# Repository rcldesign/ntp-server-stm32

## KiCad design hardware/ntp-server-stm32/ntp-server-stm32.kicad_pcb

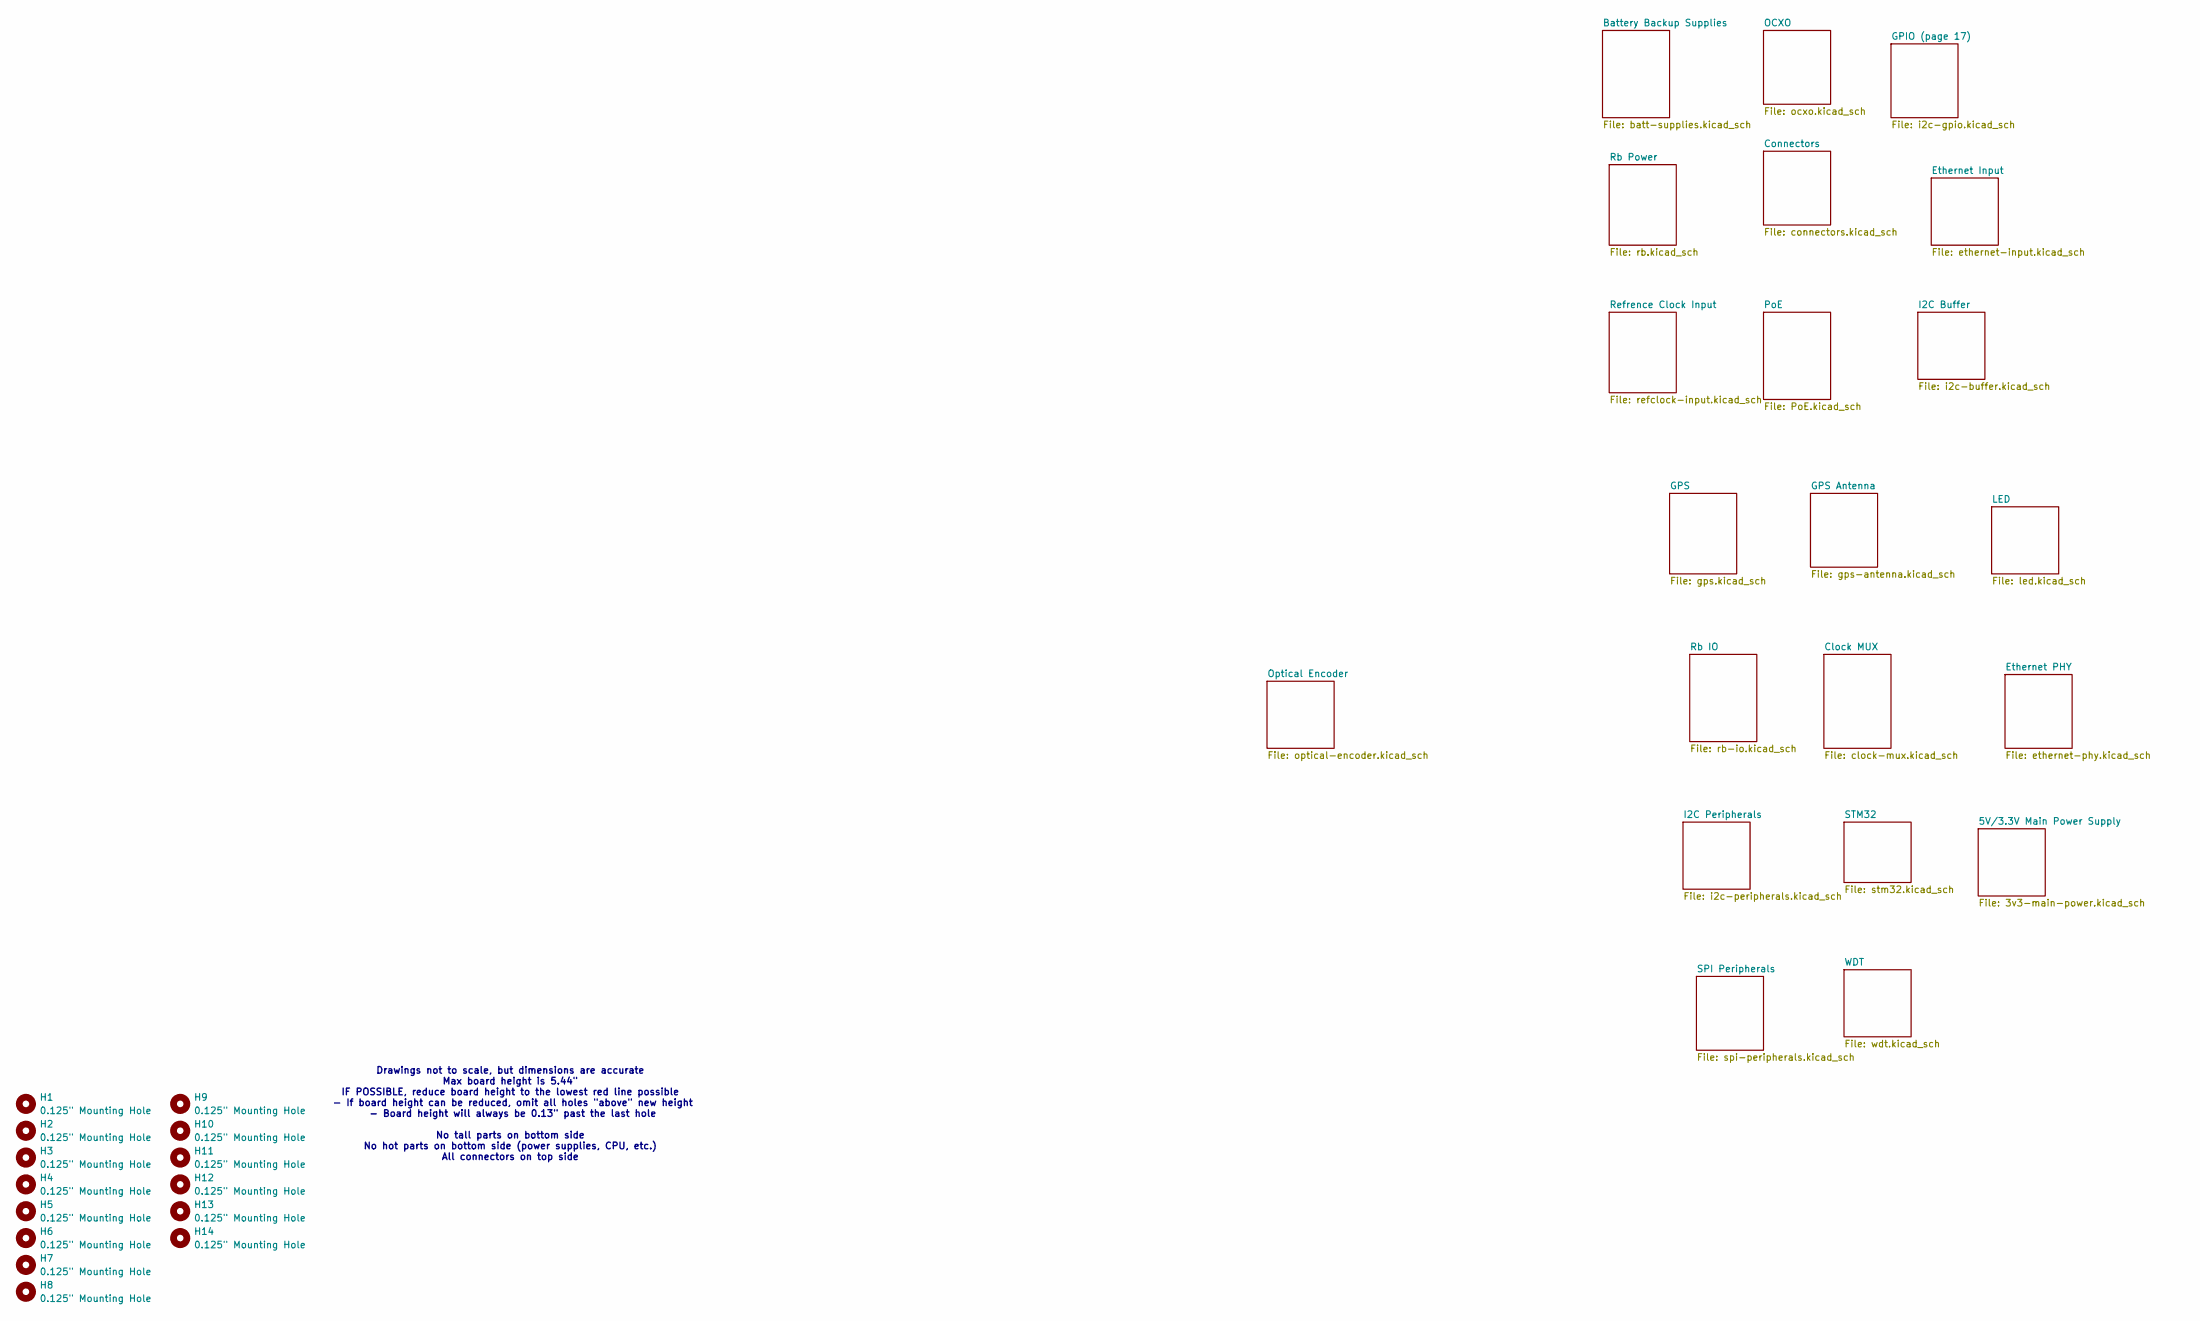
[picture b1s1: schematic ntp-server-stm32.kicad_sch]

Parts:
H1, H2, H3, H4, H5, H6, H7, H8, H9, H10, H11, H12, H13, H14: 0.125" Mounting Hole; MountingHole_3.2mm_M3

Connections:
GND: H1.1; also elsewhere on the board

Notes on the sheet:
Drawings not to scale, but dimensions are accurate Max board height is 5.44" IF POSSIBLE, reduce board height to the lowest red line possible - If board height can be reduced, omit all holes "above" new height - Board height will always be 0.13" past the last hole No tall parts on bottom side No ho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

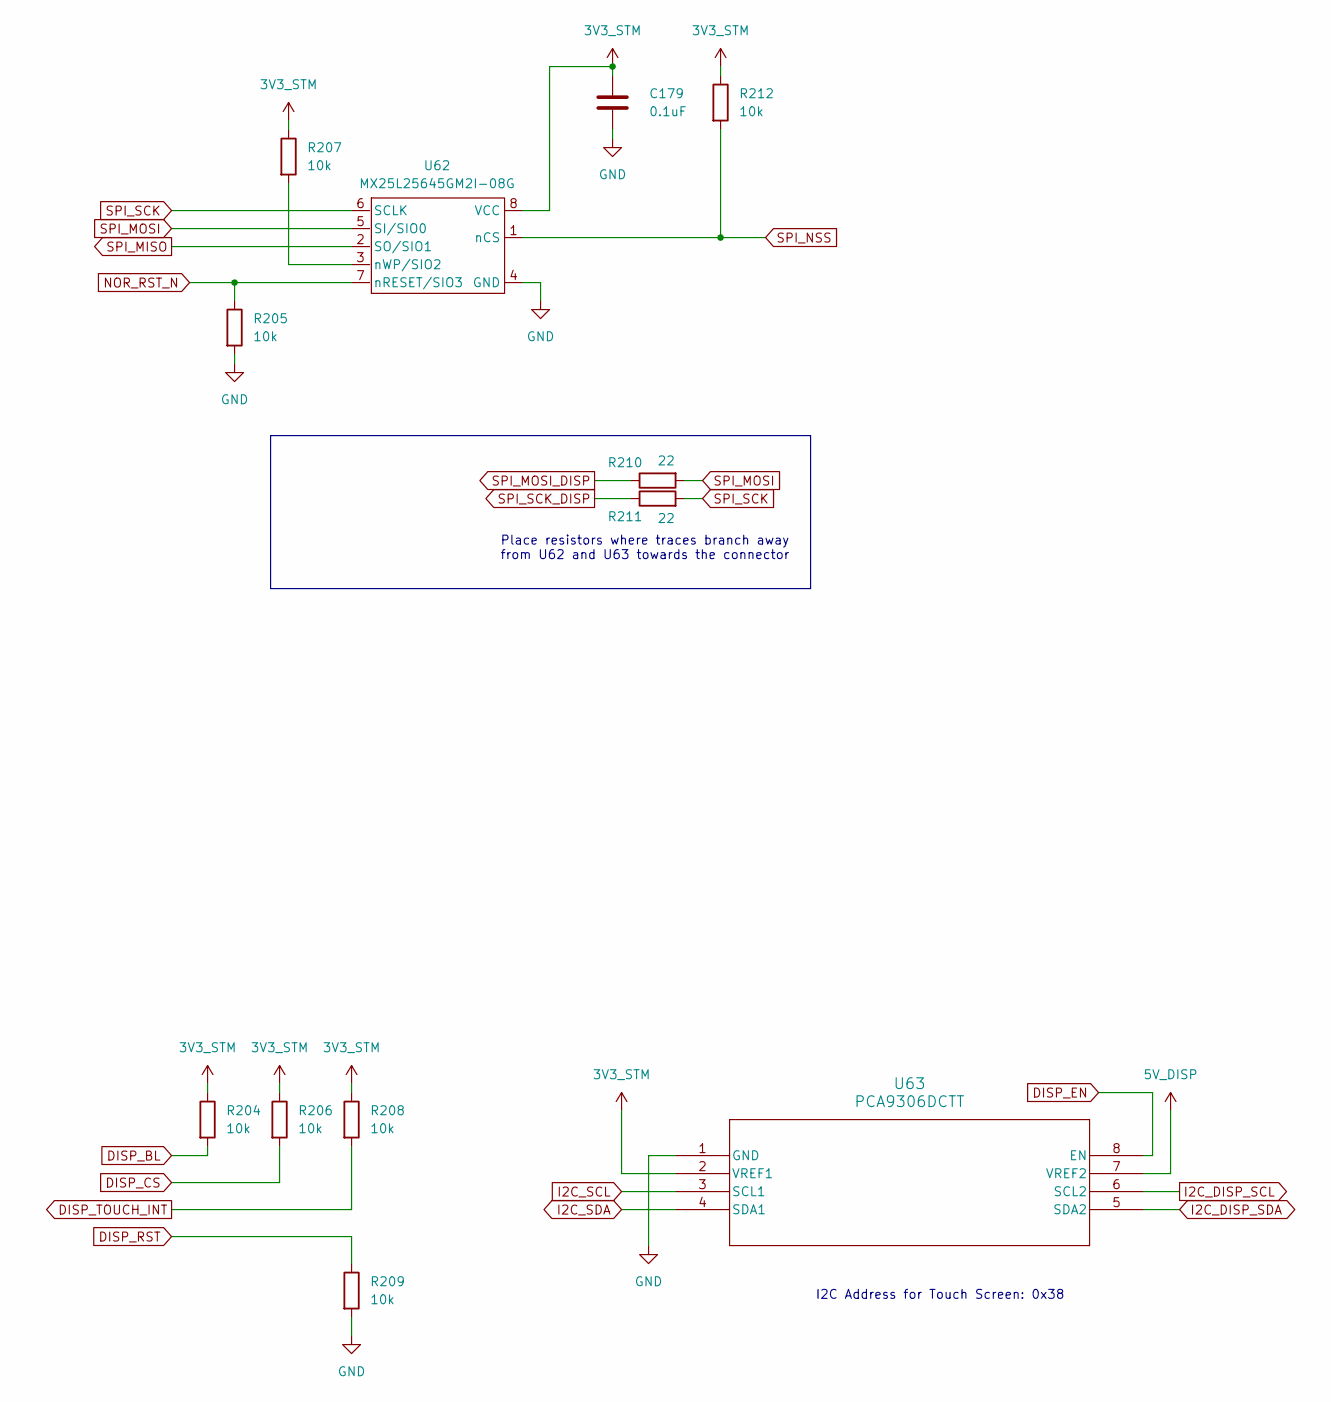
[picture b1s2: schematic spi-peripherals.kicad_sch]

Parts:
C179: 0.1uF; C_0402_1005Metric; TOLERANCE 10%; VOLTAGE 16V; MANUFACTURER_PART_NUMBER GCM155R71C104KA55D; DIGIKEY_PART_NUMBER 490-4759-1-ND
R204, R205, R206, R207, R208, R209, R212: 10k; R_0402_1005Metric; TOLERANCE 1%; MANUFACTURER_PART_NUMBER ERJ-2RKF1002X; DIGIKEY_PART_NUMBER P10.0KLCT-ND
R210, R211: 22; R_0402_1005Metric; TOLERANCE 1%; MANUFACTURER_PART_NUMBER ERJ-2RKF22R0X; DIGIKEY_PART_NUMBER P22.0LCT-ND
U62: MX25L25645GM2I-08G; SOIC-8_3.9x4.9mm_P1.27mm; MANUFACTURER_PART_NUMBER MX25L25645GM2I-08G; DIGIKEY_PART_NUMBER 1092-1234-ND
U63: PCA9306DCTT; DCT8; MANUFACTURER_PART_NUMBER PCA9306DCTT; DIGIKEY_PART_NUMBER 296-32200-1-ND

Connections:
3V3_STM: C179.1, R204.1, R206.1, R207.1, R208.1, R212.1, U62.8 (VCC), U63.2 (VREF1); also elsewhere on the board
5V_DISP: U63.7 (VREF2); also elsewhere on the board
DISP_BL: R204.2; also elsewhere on the board
DISP_CS: R206.2; also elsewhere on the board
DISP_EN: U63.8 (EN); also elsewhere on the board
DISP_RST: R209.1; also elsewhere on the board
DISP_TOUCH_INT: R208.2; also elsewhere on the board
GND: C179.2, R205.2, R209.2, U62.4 (GND), U63.1 (GND); also elsewhere on the board
I2C_DISP_SCL: U63.6 (SCL2); also elsewhere on the board
I2C_DISP_SDA: U63.5 (SDA2); also elsewhere on the board
I2C_SCL: U63.3 (SCL1); also elsewhere on the board
I2C_SDA: U63.4 (SDA1); also elsewhere on the board
NOR_RST_N: R205.1, U62.7 (nRESET/SIO3); also elsewhere on the board
unnamed: R207.2, U62.3 (nWP/SIO2)
SPI_MISO: U62.2 (SO/SIO1); also elsewhere on the board
SPI_MOSI: R210.2, U62.5 (SI/SIO0); also elsewhere on the board
SPI_MOSI_DISP: R210.1; also elsewhere on the board
SPI_NSS: R212.2, U62.1 (nCS); also elsewhere on the board
SPI_SCK: R211.2, U62.6 (SCLK); also elsewhere on the board
SPI_SCK_DISP: R211.1; also elsewhere on the board

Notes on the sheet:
Place resistors where traces branch away from U62 and U63 towards the connector
I2C Address for Touch Screen: 0x38

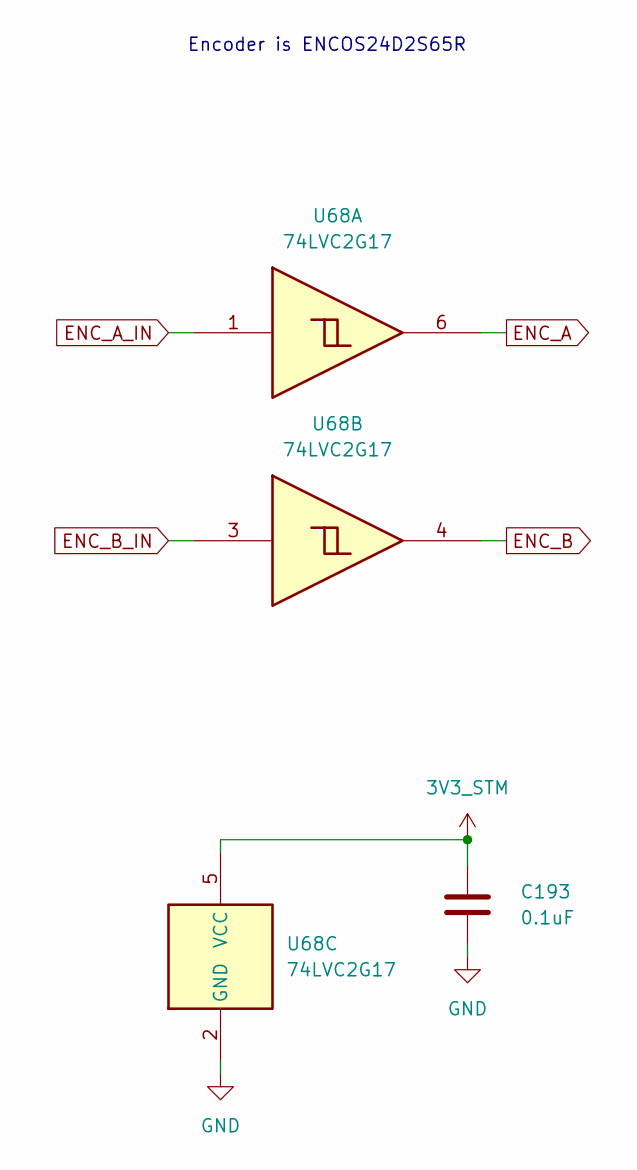
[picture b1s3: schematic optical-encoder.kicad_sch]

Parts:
C193: 0.1uF; C_0402_1005Metric; TOLERANCE 10%; VOLTAGE 16V; MANUFACTURER_PART_NUMBER GCM155R71C104KA55D; DIGIKEY_PART_NUMBER 490-4759-1-ND
U68: 74LVC2G17; 74LVC2G17GW,125; MANUFACTURER_PART_NUMBER 74LVC2G17GW,125; DIGIKEY_PART_NUMBER 1727-4218-1-ND

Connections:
3V3_STM: C193.1, U68.5 (VCC); also elsewhere on the board
ENC_A: U68.6; also elsewhere on the board
ENC_A_IN: U68.1; also elsewhere on the board
ENC_B: U68.4; also elsewhere on the board
ENC_B_IN: U68.3; also elsewhere on the board
GND: C193.2, U68.2 (GND); also elsewhere on the board

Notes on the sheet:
Encoder is ENCOS24D2S65R

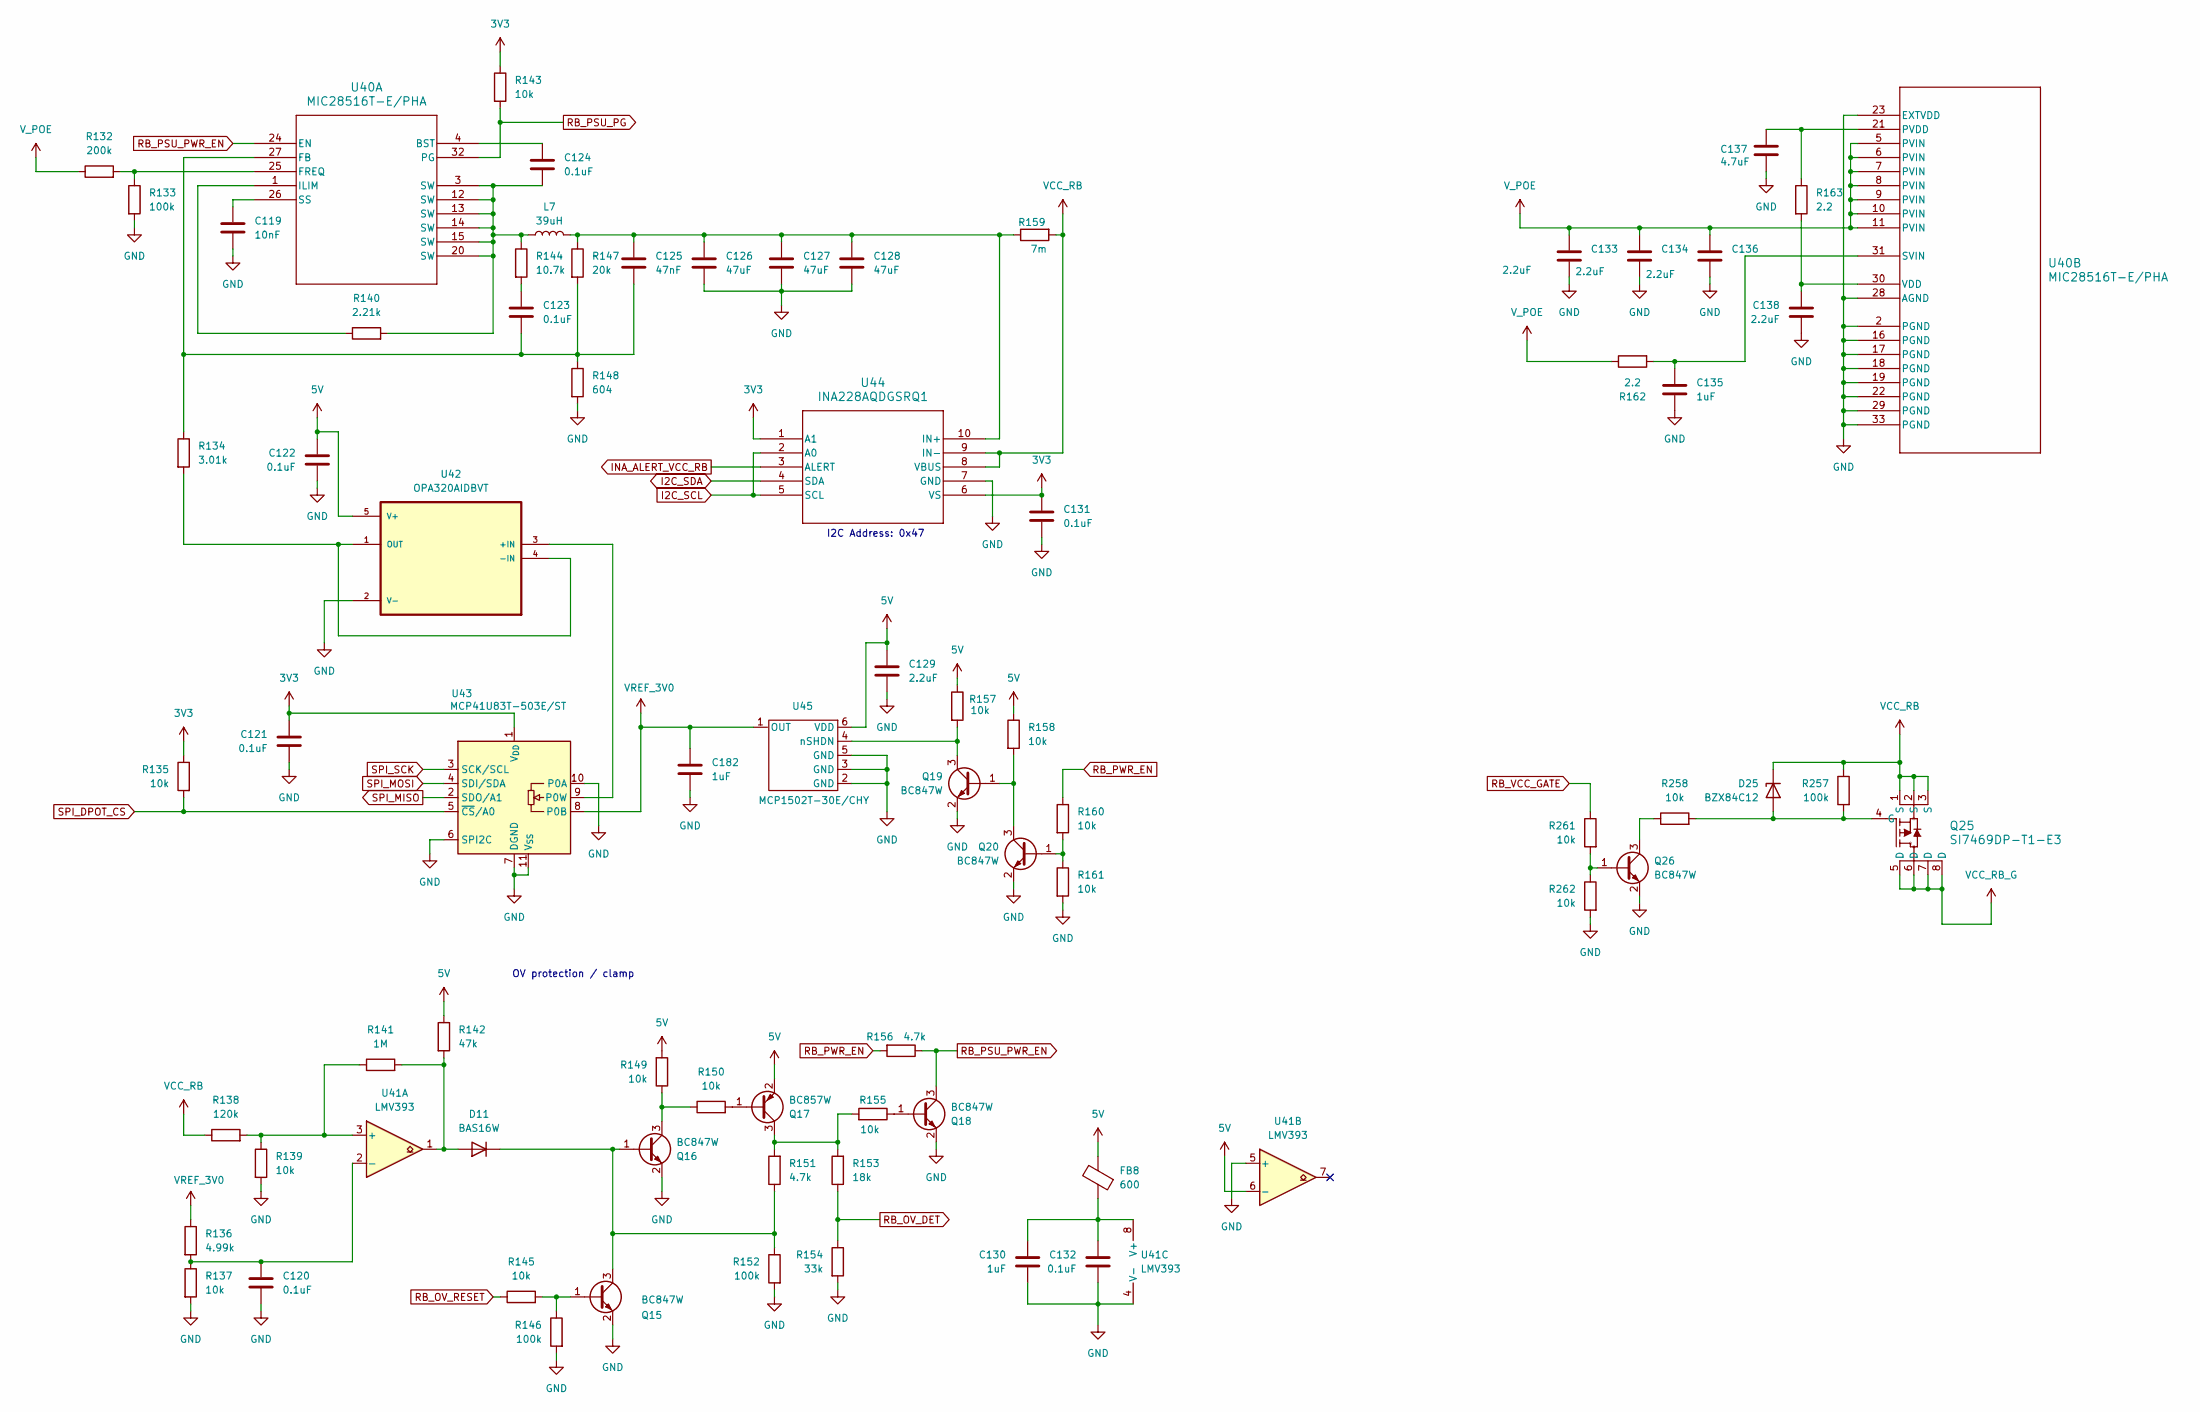
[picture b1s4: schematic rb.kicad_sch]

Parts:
C119: 10nF; C_0402_1005Metric; TOLERANCE 10%; VOLTAGE 16V; MANUFACTURER_PART_NUMBER GRT155R71C103KE01J; DIGIKEY_PART_NUMBER 490-GRT155R71C103KE01JCT-ND
C120, C121, C122, C123, C124, C131, C132: 0.1uF; C_0402_1005Metric; TOLERANCE 10%; VOLTAGE 16V; MANUFACTURER_PART_NUMBER GCM155R71C104KA55D; DIGIKEY_PART_NUMBER 490-4759-1-ND
C125: 47nF; C_0402_1005Metric; TOLERANCE 10%; VOLTAGE 50V; MANUFACTURER_PART_NUMBER GCM155R71H473KE02J; DIGIKEY_PART_NUMBER 490-14515-1-ND
C126, C127, C128: 47uF; KCM55WR71H476MH13L; TOLERANCE 10%; VOLTAGE 50V; MANUFACTURER_PART_NUMBER KCM55WR71H476MH13L; DIGIKEY_PART_NUMBER 490-KCM55WR71H476MH13LCT-ND
C129, C138: 2.2uF; C_0805_2012Metric; TOLERANCE 10%; VOLTAGE 16V; MANUFACTURER_PART_NUMBER GRT21BR71C225KE01L; DIGIKEY_PART_NUMBER 490-GRT21BR71C225KE01LCT-ND
C130, C182: 1uF; C_0603_1608Metric; TOLERANCE 10%; VOLTAGE 16V; MANUFACTURER_PART_NUMBER C0603C105K4RACAUTO; DIGIKEY_PART_NUMBER 399-17704-1-ND
C133, C134, C136: 2.2uF; C_2220_5750Metric; TOLERANCE 10%; VOLTAGE 100V; MANUFACTURER_PART_NUMBER CGA9P3X7T2E225K250KA; DIGIKEY_PART_NUMBER 445-7950-1-ND
C135: 1uF; C_0805_2012Metric; TOLERANCE 10%; VOLTAGE 100V; MANUFACTURER_PART_NUMBER 08051C105K4T2A; DIGIKEY_PART_NUMBER 478-KAM21KR72A105KUCT-ND
C137: 4.7uF; C_0805_2012Metric; TOLERANCE 10%; VOLTAGE 16V; MANUFACTURER_PART_NUMBER GRT21BR71C475KE13K; DIGIKEY_PART_NUMBER 490-GRT21BR71C475KE13KCT-ND
D11: BAS16W; SOD-123; MANUFACTURER_PART_NUMBER BAS16WHE3-TP; DIGIKEY_PART_NUMBER 353-BAS16WHE3-TPCT-ND
D25: BZX84C12; SOT-23-3; MANUFACTURER_PART_NUMBER BZX84C12LT1G; DIGIKEY_PART_NUMBER BZX84C12LT1GOSCT-ND
FB8: 600; 1206; MANUFACTURER_PART_NUMBER BLM31PG601SN1L; DIGIKEY_PART_NUMBER 490-16533-1-ND
L7: 39uH; 7447709390; MANUFACTURER_PART_NUMBER 7447709390; DIGIKEY_PART_NUMBER 732-7447709390CT-ND
Q15, Q16, Q18, Q19, Q20, Q26: BC847W; SOT-323_SC-70; MANUFACTURER_PART_NUMBER BC847W,135; DIGIKEY_PART_NUMBER 1727-BC847W,135CT-ND
Q17: BC857W; SOT-323_SC-70; MANUFACTURER_PART_NUMBER BC857W,135; DIGIKEY_PART_NUMBER 1727-BC857W,135CT-ND
Q25: SI7469DP-T1-E3; PowerPAKÂ® SO-8; MANUFACTURER_PART_NUMBER SI7469DP-T1-E3; DIGIKEY_PART_NUMBER SI7469DP-T1-E3CT-ND
R132: 200k; R_0402_1005Metric; TOLERANCE 1%; MANUFACTURER_PART_NUMBER ERJ-2RKF2003X; DIGIKEY_PART_NUMBER P200KLCT-ND
R133, R146, R152, R257: 100k; R_0402_1005Metric; TOLERANCE 1%; MANUFACTURER_PART_NUMBER ERJ-2RKF1003X; DIGIKEY_PART_NUMBER P100KLCT-ND
R134: 3.01k; R_0402_1005Metric; TOLERANCE 1%; MANUFACTURER_PART_NUMBER RK73H1ETTP3011F; DIGIKEY_PART_NUMBER 2019-RK73H1ETTP3011FCT-ND
R135, R137, R139, R143, R145, R149, R150, R155, R157, R158, R160, R161, R258, R261, R262: 10k; R_0402_1005Metric; TOLERANCE 1%; MANUFACTURER_PART_NUMBER ERJ-2RKF1002X; DIGIKEY_PART_NUMBER P10.0KLCT-ND
R136: 4.99k; R_0402_1005Metric; TOLERANCE 1%; MANUFACTURER_PART_NUMBER ERJ-2RKF4991X; DIGIKEY_PART_NUMBER P4.99KLCT-ND
R138: 120k; R_0402_1005Metric; TOLERANCE 1%; MANUFACTURER_PART_NUMBER ERJ-2RKF1203X; DIGIKEY_PART_NUMBER P120KLCT-ND
R140: 2.21k; R_0402_1005Metric; TOLERANCE 1%; MANUFACTURER_PART_NUMBER ERJ-2RKF2211X; DIGIKEY_PART_NUMBER P2.21KLCT-ND
R141: 1M; R_0402_1005Metric; TOLERANCE 1%; MANUFACTURER_PART_NUMBER ERJ-2RKF1004X; DIGIKEY_PART_NUMBER P1.00MLCT-ND
R142: 47k; R_0402_1005Metric; TOLERANCE 1%; MANUFACTURER_PART_NUMBER ERJ-2RKF4702X; DIGIKEY_PART_NUMBER P47.0KLCT-ND
R144: 10.7k; R_0402_1005Metric; TOLERANCE 1%; MANUFACTURER_PART_NUMBER ERJ-2RKF1072X; DIGIKEY_PART_NUMBER P10.7KLCT-ND
R147: 20k; R_0402_1005Metric; TOLERANCE 1%; MANUFACTURER_PART_NUMBER ERJ-H2RD2002X; DIGIKEY_PART_NUMBER 10-ERJ-H2RD2002XCT-ND
R148: 604; R_0402_1005Metric; TOLERANCE 1%; MANUFACTURER_PART_NUMBER ERJ-2RKF6040X; DIGIKEY_PART_NUMBER P604LCT-ND
R151, R156: 4.7k; R_0402_1005Metric; TOLERANCE 1%; MANUFACTURER_PART_NUMBER ERJ-2RKF4701X; DIGIKEY_PART_NUMBER P4.70KLCT-ND
R153: 18k; R_0402_1005Metric; TOLERANCE 1%; MANUFACTURER_PART_NUMBER ERJ-2RKF1802X; DIGIKEY_PART_NUMBER P18.0KLCT-ND
R154: 33k; R_0402_1005Metric; TOLERANCE 1%; MANUFACTURER_PART_NUMBER ERJ-2RKF3302X; DIGIKEY_PART_NUMBER P33.0KLCT-ND
R159: 7m; R_2512_6332Metric; TOLERANCE 0.5%; MANUFACTURER_PART_NUMBER WSL25127L000FEA; DIGIKEY_PART_NUMBER WSLG-.007CT-ND
R162, R163: 2.2; R_0402_1005Metric; TOLERANCE 1%; MANUFACTURER_PART_NUMBER ERJ-U02F2R20X; DIGIKEY_PART_NUMBER 10-ERJ-U02F2R20XTR-ND
U40: MIC28516T-E/PHA; MIC28516T-EPHA; MANUFACTURER_PART_NUMBER MIC28516T-E/PHA; DIGIKEY_PART_NUMBER 150-MIC28516T-E/PHATR-ND
U41: LMV393; MANUFACTURER_PART_NUMBER LMV393IDGKR; DIGIKEY_PART_NUMBER 296-13993-1-ND
U42: OPA320AIDBVT; SOT95P280X145-5N; MANUFACTURER_PART_NUMBER OPA320AIDBVT; DIGIKEY_PART_NUMBER 296-29510-1-ND
U43: MCP41U83T-503E/ST; TSSOP-14_4.4x5mm_P0.65mm; MANUFACTURER_PART_NUMBER MCP41U83T-503E/ST; DIGIKEY_PART_NUMBER 150-MCP41U83T-503E/STCT-ND
U44: INA228AQDGSRQ1; VSSOP10_DGS_TEX; MANUFACTURER_PART_NUMBER INA228AQDGSRQ1; DIGIKEY_PART_NUMBER 296-INA228AQDGSRQ1CT-ND
U45: MCP1502T-30E/CHY; SOT-23-6; MANUFACTURER_PART_NUMBER MCP1502T-30E/CHY; DIGIKEY_PART_NUMBER 150-MCP1502T-30E/CHYCT-ND

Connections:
3V3: C121.1, C131.1, R135.1, R143.1, U43.1 (V_{DD}), U44.1 (A1), U44.6 (VS); also elsewhere on the board
5V: C122.1, C129.1, FB8.2, Q17.2 (E), R142.1, R149.2, R157.1, R158.1, U41.6 (-), U42.5 (V+), U45.6 (VDD); also elsewhere on the board
GND: C119.2, C120.2, C121.2, C122.2, C126.2, C127.2, C128.2, C129.2, C130.2, C131.2, C132.2, C133.2, C134.2, C135.2, C136.2, C137.2, C138.2, C182.2, Q15.2 (E), Q16.2 (E), Q18.2 (E), Q19.2 (E), Q20.2 (E), Q26.2 (E), R133.2, R137.2, R139.2, R146.2, R148.2, R152.2, R154.2, R161.2, R262.2, U40.2 (PGND), U40.16 (PGND), U40.17 (PGND), U40.18 (PGND), U40.19 (PGND), U40.22 (PGND), U40.23 (EXTVDD), U40.28 (AGND), U40.29 (PGND), U40.33 (PGND), U41.4 (V-), U41.5 (+), U42.2 (V-), U43.6 (SPI2C), U43.7 (DGND), U43.10 (P0A), U43.11 (V_{SS}), U44.7 (GND), U45.2 (GND), U45.3 (GND), U45.5 (GND); also elsewhere on the board
I2C_SCL: U44.2 (A0), U44.5 (SCL); also elsewhere on the board
I2C_SDA: U44.4 (SDA); also elsewhere on the board
INA_ALERT_VCC_RB: U44.3 (ALERT); also elsewhere on the board
unnamed: C123.1, R144.2
unnamed: C124.2, L7.1, R140.2, R144.1, U40.3 (SW), U40.12 (SW), U40.13 (SW), U40.14 (SW), U40.15 (SW), U40.20 (SW)
unnamed: D11.1 (A), R141.2, R142.2, U41.1
unnamed: D11.3 (K), Q15.3 (C), Q16.1 (B), R151.1, R152.1
unnamed: D25.2 (A), Q25.4 (G), R257.2, R258.2
unnamed: Q15.1 (B), R145.2, R146.1
unnamed: Q16.3 (C), R149.1, R150.1
unnamed: Q17.1 (B), R150.2
unnamed: Q17.3 (C), R151.2, R153.2, R155.2
unnamed: Q18.1 (B), R155.1
unnamed: Q19.1 (B), Q20.3 (C), R158.2
unnamed: Q19.3 (C), R157.2, U45.4 (nSHDN)
unnamed: Q20.1 (B), R160.2, R161.1
unnamed: Q26.1 (B), R261.2, R262.1
unnamed: Q26.3 (C), R258.1
unnamed: C124.1, U40.4 (BST)
unnamed: C123.2, C125.2, R134.1, R147.2, R148.1, U40.27 (FB)
unnamed: R132.2, R133.1, U40.25 (FREQ)
unnamed: R140.1, U40.1 (ILIM)
unnamed: C119.1, U40.26 (SS)
unnamed: C137.1, R163.1, U40.21 (PVDD)
unnamed: C135.1, R162.2, U40.31 (SVIN)
unnamed: C138.1, R163.2, U40.30 (VDD)
unnamed: R138.2, R139.1, R141.1, U41.3 (+)
unnamed: C120.1, R136.2, R137.1, U41.2 (-)
unnamed: C130.1, C132.1, FB8.1, U41.8 (V+)
unnamed: U42.3 (+IN), U43.9 (P0W)
unnamed: R134.2, U42.1 (OUT), U42.4 (-IN)
unnamed: C125.1, C126.1, C127.1, C128.1, L7.2, R147.1, R159.1, U44.10 (IN+)
RB_OV_DET: R153.1, R154.1; also elsewhere on the board
RB_OV_RESET: R145.1; also elsewhere on the board
RB_PSU_PG: R143.2, U40.32 (PG); also elsewhere on the board
RB_PSU_PWR_EN: Q18.3 (C), R156.1, U40.24 (EN)
RB_PWR_EN: R156.2, R160.1; also elsewhere on the board
RB_VCC_GATE: R261.1; also elsewhere on the board
SPI_DPOT_CS: R135.2, U43.5 (~CS/A0); also elsewhere on the board
SPI_MISO: U43.2 (SDO/A1); also elsewhere on the board
SPI_MOSI: U43.4 (SDI/SDA); also elsewhere on the board
SPI_SCK: U43.3 (SCK/SCL); also elsewhere on the board
VCC_RB: D25.1 (K), Q25.1 (S), Q25.2 (S), Q25.3 (S), R138.1, R159.2, R257.1, U44.8 (VBUS), U44.9 (IN-)
VCC_RB_G: Q25.5 (D), Q25.6 (D), Q25.7 (D), Q25.8 (D); also elsewhere on the board
VREF_3V0: C182.1, R136.1, U43.8 (P0B), U45.1 (OUT)
V_POE: C133.1, C134.1, C136.1, R132.1, R162.1, U40.5 (PVIN), U40.6 (PVIN), U40.7 (PVIN), U40.8 (PVIN), U40.9 (PVIN), U40.10 (PVIN), U40.11 (PVIN); also elsewhere on the board

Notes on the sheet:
I2C Address: 0x47
OV protection / clamp

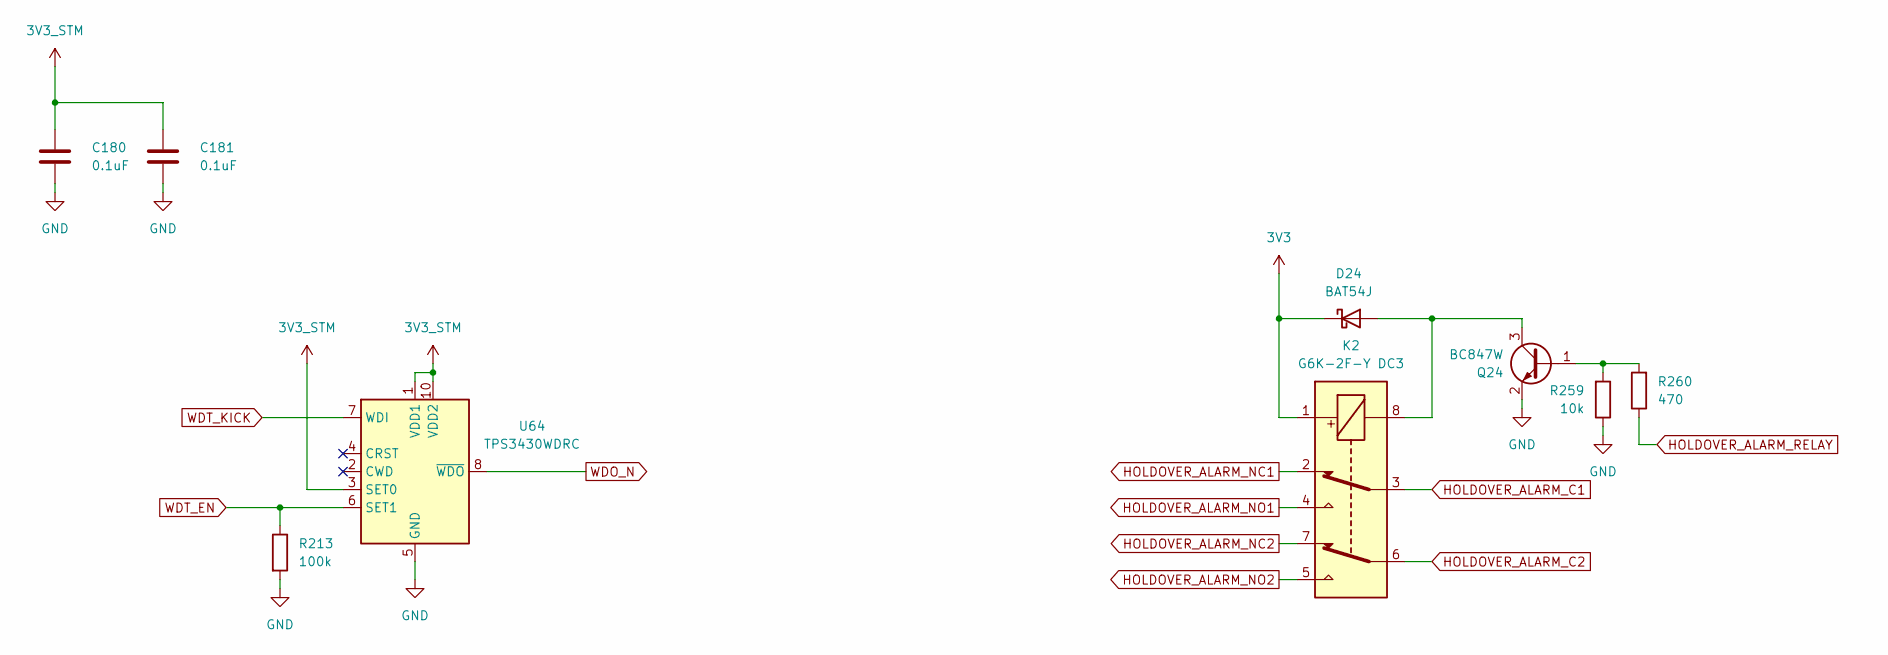
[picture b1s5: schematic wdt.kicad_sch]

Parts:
C180, C181: 0.1uF; C_0402_1005Metric; TOLERANCE 10%; VOLTAGE 16V; MANUFACTURER_PART_NUMBER GCM155R71C104KA55D; DIGIKEY_PART_NUMBER 490-4759-1-ND
D24: BAT54J; D_SOD-323F; MANUFACTURER_PART_NUMBER BAT54J-QX; DIGIKEY_PART_NUMBER 1727-BAT54J-QXCT-ND
K2: G6K-2F-Y DC3; MANUFACTURER_PART_NUMBER G6K-2F-Y DC3; DIGIKEY_PART_NUMBER 39-G6K-2F-YDC3-ND
Q24: BC847W; SOT-323_SC-70; MANUFACTURER_PART_NUMBER BC847W,135; DIGIKEY_PART_NUMBER 1727-BC847W,135CT-ND
R213: 100k; R_0402_1005Metric; TOLERANCE 1%; MANUFACTURER_PART_NUMBER ERJ-2RKF1003X; DIGIKEY_PART_NUMBER P100KLCT-ND
R259: 10k; R_0402_1005Metric; TOLERANCE 1%; MANUFACTURER_PART_NUMBER ERJ-2RKF1002X; DIGIKEY_PART_NUMBER P10.0KLCT-ND
R260: 470; R_0402_1005Metric; TOLERANCE 1%; MANUFACTURER_PART_NUMBER ERJ-2RKF4700X; DIGIKEY_PART_NUMBER P470LCT-ND
U64: TPS3430WDRC; VSON-10-1EP_3x3mm_P0.5mm_EP1.65x2.4mm; MANUFACTURER_PART_NUMBER TPS3430WDRC; DIGIKEY_PART_NUMBER 296-51907-1-ND

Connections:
3V3: D24.1 (K), K2.1; also elsewhere on the board
3V3_STM: C180.1, C181.1, U64.1 (VDD1), U64.3 (SET0), U64.10 (VDD2); also elsewhere on the board
GND: C180.2, C181.2, Q24.2 (E), R213.2, R259.1, U64.5 (GND), U64.11 (GND); also elsewhere on the board
HOLDOVER_ALARM_C1: K2.3; also elsewhere on the board
HOLDOVER_ALARM_C2: K2.6; also elsewhere on the board
HOLDOVER_ALARM_NC1: K2.2; also elsewhere on the board
HOLDOVER_ALARM_NC2: K2.7; also elsewhere on the board
HOLDOVER_ALARM_NO1: K2.4; also elsewhere on the board
HOLDOVER_ALARM_NO2: K2.5; also elsewhere on the board
HOLDOVER_ALARM_RELAY: R260.1; also elsewhere on the board
unnamed: D24.2 (A), K2.8, Q24.3 (C)
unnamed: Q24.1 (B), R259.2, R260.2
WDO_N: U64.8 (~WDO); also elsewhere on the board
WDT_EN: R213.1, U64.6 (SET1); also elsewhere on the board
WDT_KICK: U64.7 (WDI); also elsewhere on the board

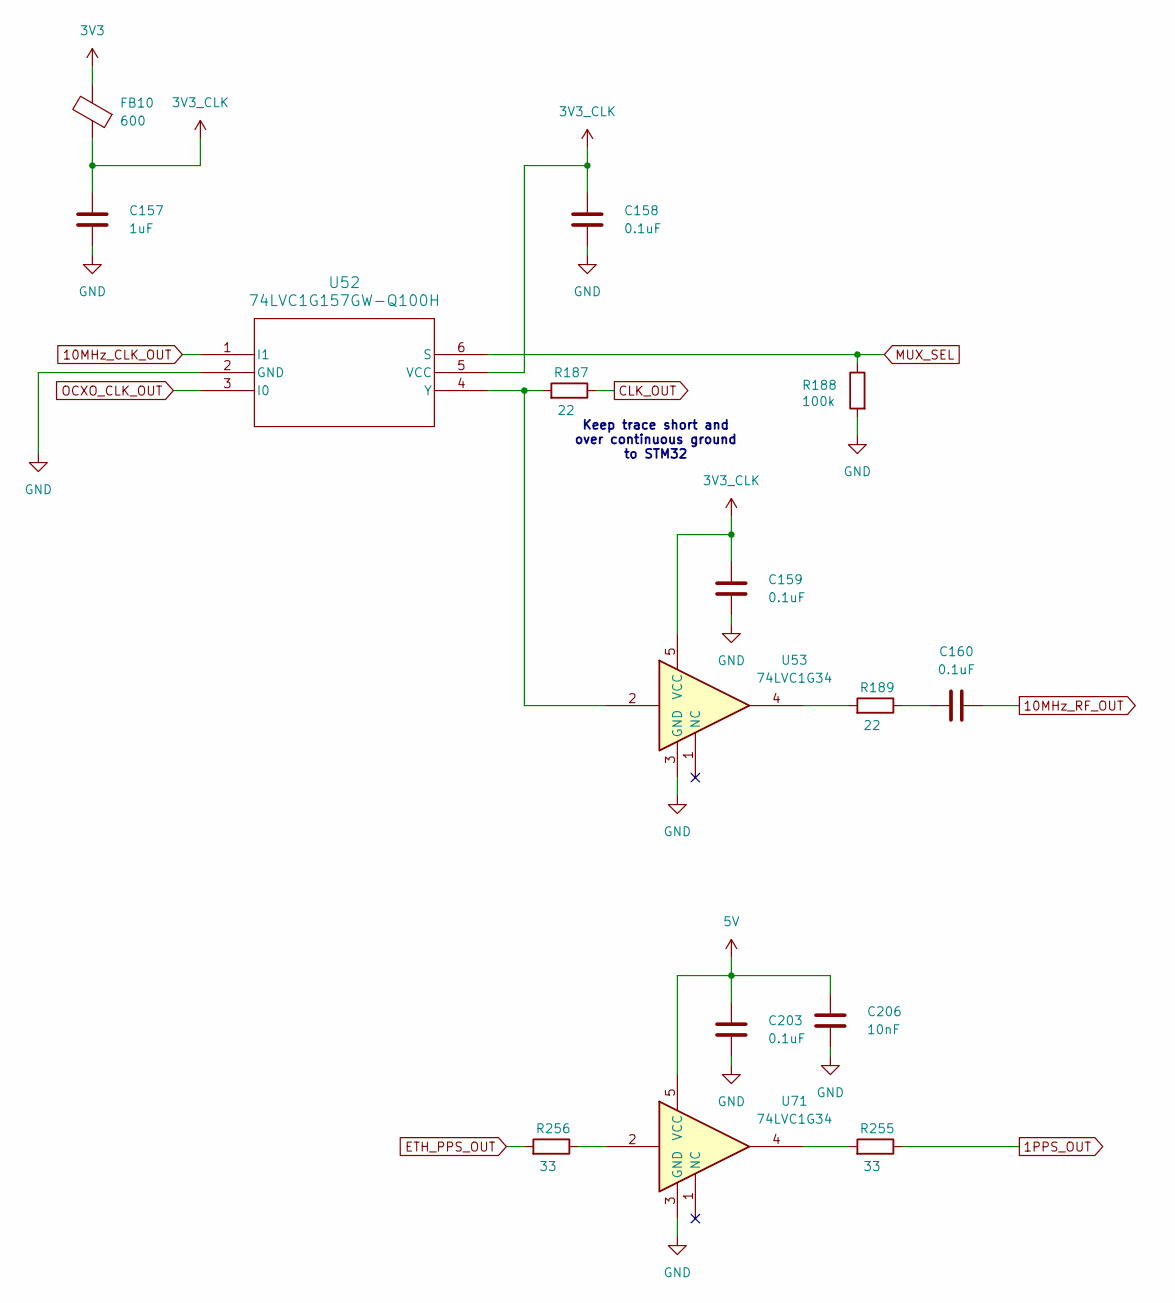
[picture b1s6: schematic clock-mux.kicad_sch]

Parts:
C157: 1uF; C_0603_1608Metric; TOLERANCE 10%; VOLTAGE 16V; MANUFACTURER_PART_NUMBER C0603C105K4RACAUTO; DIGIKEY_PART_NUMBER 399-17704-1-ND
C158, C159, C160, C203: 0.1uF; C_0402_1005Metric; TOLERANCE 10%; VOLTAGE 16V; MANUFACTURER_PART_NUMBER GCM155R71C104KA55D; DIGIKEY_PART_NUMBER 490-4759-1-ND
C206: 10nF; C_0402_1005Metric; TOLERANCE 10%; VOLTAGE 16V; MANUFACTURER_PART_NUMBER GRT155R71C103KE01J; DIGIKEY_PART_NUMBER 490-GRT155R71C103KE01JCT-ND
FB10: 600; 1206; MANUFACTURER_PART_NUMBER BLM31PG601SN1L; DIGIKEY_PART_NUMBER 490-16533-1-ND
R187, R189: 22; R_0402_1005Metric; TOLERANCE 1%; MANUFACTURER_PART_NUMBER ERJ-2RKF22R0X; DIGIKEY_PART_NUMBER P22.0LCT-ND
R188: 100k; R_0402_1005Metric; TOLERANCE 1%; MANUFACTURER_PART_NUMBER ERJ-2RKF1003X; DIGIKEY_PART_NUMBER P100KLCT-ND
R255, R256: 33; R_0402_1005Metric; TOLERANCE 1%; MANUFACTURER_PART_NUMBER ERJ-2RKF33R0X; DIGIKEY_PART_NUMBER P33.0LCT-ND
U52: 74LVC1G157GW-Q100H; SC-74_TSOP6_SOT457_NEX; MANUFACTURER_PART_NUMBER 74LVC1G157GW-Q100H; DIGIKEY_PART_NUMBER 1727-74LVC1G157GW-Q100HCT-ND
U53, U71: 74LVC1G34; 74LVC1G34GW_125; MANUFACTURER_PART_NUMBER 74LVC1G34GW,125; DIGIKEY_PART_NUMBER 1727-6074-1-ND

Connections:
1PPS_OUT: R255.1; also elsewhere on the board
3V3: FB10.2; also elsewhere on the board
3V3_CLK: C157.1, C158.1, C159.1, FB10.1, U52.5 (VCC), U53.5 (VCC)
5V: C203.1, C206.1, U71.5 (VCC); also elsewhere on the board
10MHz_CLK_OUT: U52.1 (I1); also elsewhere on the board
10MHz_RF_OUT: C160.2; also elsewhere on the board
CLK_OUT: R187.1; also elsewhere on the board
ETH_PPS_OUT: R256.2; also elsewhere on the board
GND: C157.2, C158.2, C159.2, C203.2, C206.2, R188.2, U52.2 (GND), U53.3 (GND), U71.3 (GND); also elsewhere on the board
MUX_SEL: R188.1, U52.6 (S); also elsewhere on the board
unnamed: C160.1, R189.1
unnamed: R189.2, U53.4
unnamed: R255.2, U71.4
unnamed: R256.1, U71.2
unnamed: R187.2, U52.4 (Y), U53.2
OCXO_CLK_OUT: U52.3 (I0); also elsewhere on the board

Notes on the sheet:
Keep trace short and over continuous ground to STM32
